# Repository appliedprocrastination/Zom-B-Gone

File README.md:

# Zom-B-Gone

Code for a very basic DIY Wake-up Light. 

This code uses an Arduino Nano (Uno would also work)
It assumes that an Adafruit DS3231 RTC module is connected to the following pins:
 * SDA = A4
 * SCL = A5
 * SQW = D3

The code further assumes a rotary encoder connected to the following pins:
 * CLK = A0
 * DT = A1
 * SW = A2

It is finally assumed that an ULN2803N is connected to pin D6, and that there is a button connected to pin D2.
The button used in the original code includes an LED that is connected to pin D6,
and connecting an LED to this pin will indicate whenever the WakeUpLight is in manual override mode.

To change the alarm settings, modify the `AlarmSettings` struct with your preffered values. Current behavior of the wake-up light is to dim up for 30 minutes towards the START alarm and then down for 30 minutes towards the END alarm. This is inteded to be synced with an external alarm clock (eg. cell phone alarm).

Before first use: set the correct time on the RTC module and load it with a coin cell battery to retain this value through power cycles.

by:
[Applied Procrastination](https://www.youtube.com/AppliedProcrastination)

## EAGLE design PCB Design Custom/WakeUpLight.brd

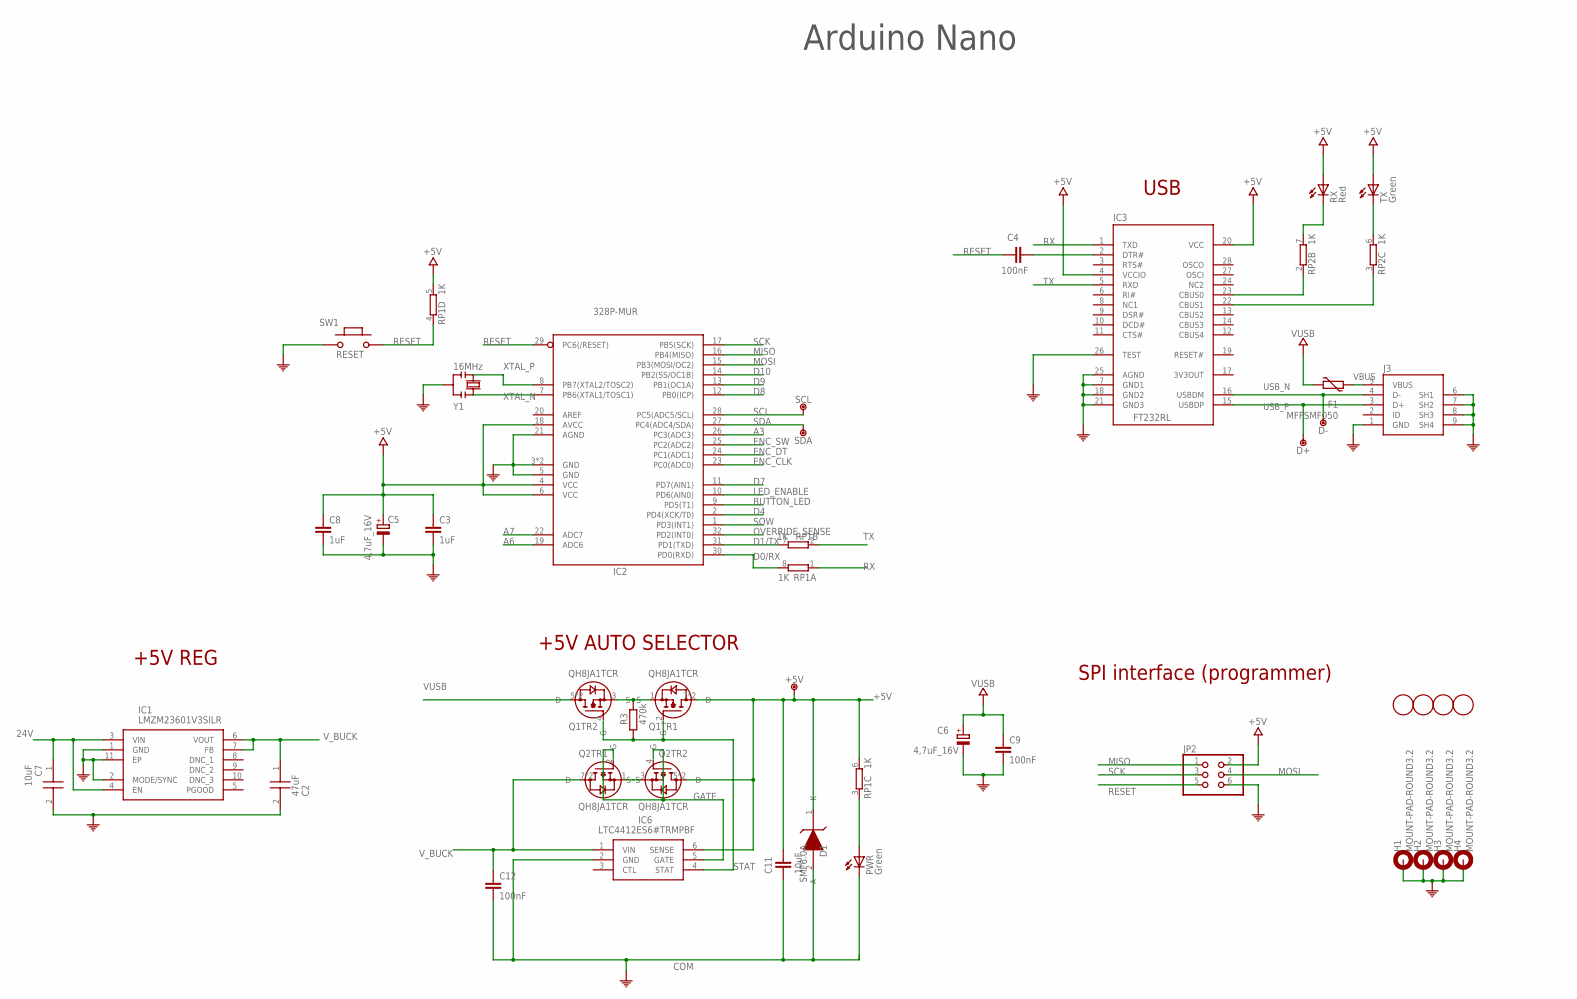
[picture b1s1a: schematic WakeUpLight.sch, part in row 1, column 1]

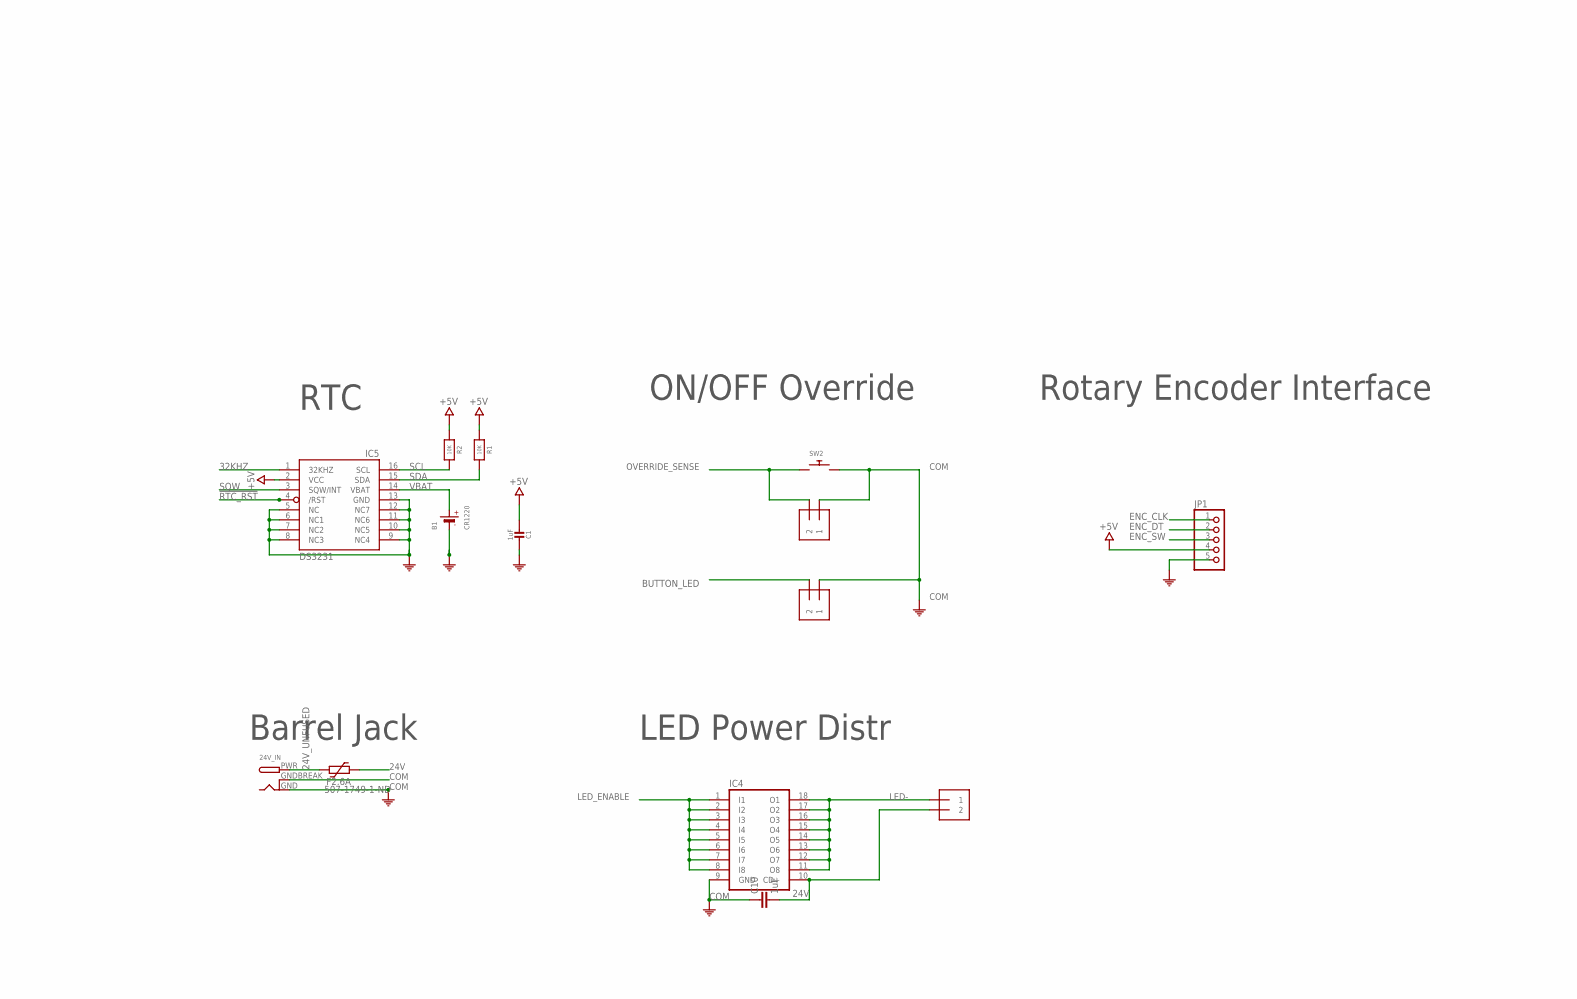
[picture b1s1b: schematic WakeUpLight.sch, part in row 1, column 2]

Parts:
24V_IN: DCBARRELPTH; DCJACK_2MM_PTH
+5V: DNP; TP-1.00MM
B1: CR1220
BUTTON_LED: 1X2-3.5MM
C1: 1uF; 0805-NO
C2: 47uF; CAPC3216X180N
C3, C8, C10: 1uF; C0603-ROUND
C4, C9, C12: 100nF; C0603-ROUND
C5, C6: 4,7uF_16V; TAN-A
C7: 10uF; CAPC2012X100N
C11: 10uF; C0603; MPN GRM188R61E106MA73D
D1: SMF6.0A; SODFL3618X108N
D+: DNP; TP-1.00MM
D-: DNP; TP-1.00MM
F1: MFFSMF050; 0603-1608X90N
F2.6A: 507-1749-1-ND; 2016L; MPN 0ZCF0200AF2C
H1, H2, H3, H4: MOUNT-PAD-ROUND3.2; 3,2-PAD
IC1: LMZM23601V3SILR; LMZM23600SILT
IC2: 328P-MUR; VQFN32
IC3: FT232RL; SSOP28
IC4: ULN2803ASMT; SO18W
IC5: DS3231/SO; SO16W
IC6: LTC4412ES6#TRMPBF; SOT95P280X100-6N
J3: 0219_14850; USB-MINI-B_2
JP1: PINHD-1X5; 1X05
JP2: 0114_PH254-203DF118A00V; 2X03
LED: 1X2-3.5MM
OVERRIDE: 1X2-3.5MM
PWR: Green; CHIPLED_0805
Q1, Q2: QH8JA1TCR; SOTFL65P280X85-8N
R1, R2: 10K; 0805-NO
R3: 470k; R0603
RP1, RP2: 1K; CAY16
RX: Red; CHIPLED_0805
SCL: DNP; TP-1.00MM
SDA: DNP; TP-1.00MM
SW1: RESET; SMD_157SW
SW2: SWITCH_PUSHBUTTONSOFTTOUCHSMD_SJ; PUSHBUTTON_SMD_SJ
TX: Green; CHIPLED_0805
U$36, U$39, U$53, U$54: DNP; FD-1-1.5
Y1: 16MHz; RESONATOR

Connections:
3V3OUT: IC3.17 (3V3OUT)
24V: C7.1, C10.2, F2.6A.2, IC1.3 (VIN), IC1.4 (EN), IC4.10 (CD+), LED.2
24V_UNFUSED: 24V_IN.PWR, F2.6A.1
32KHZ: IC5.1 (32KHZ)
!RTC_RST: IC5.4 (/RST)
+5V: +5V.X, C1.2, C3.1, C5.1 (+), C8.1, C11.1, D1.1 (K), IC2.4 (VCC), IC2.6 (VCC), IC2.18 (AVCC), IC3.4 (VCCIO), IC3.20 (VCC), IC5.2 (VCC), IC6.6 (SENSE), JP1.4, JP2.2, Q1.7 (D), Q1.8 (D), Q2.5 (D), Q2.6 (D), R1.1, R2.1, RP1.5 (2), RP1.6 (2), RX.A, TX.A
A3: IC2.26 (PC3(ADC3))
A6: IC2.19 (ADC6)
A7: IC2.22 (ADC7)
BUTTON_LED: BUTTON_LED.2, IC2.9 (PD5(T1))
COM: 24V_IN.GND, 24V_IN.GNDBREAK, B1.-, BUTTON_LED.1, C1.1, C2.2, C3.2, C5.2 (-), C6.2 (-), C7.2, C8.2, C9.2, C10.1, C11.2, C12.2, D1.2 (A), H1.B3,2, H2.B3,2, H3.B3,2, H4.B3,2, IC1.1 (GND), IC1.2 (MODE/SYNC), IC1.11 (EP), IC2.3 (GND), IC2.5 (GND), IC2.21 (AGND), IC2.33 (GND), IC3.7 (GND1), IC3.18 (GND2), IC3.21 (GND3), IC3.25 (AGND), IC3.26 (TEST), IC4.9 (GND), IC5.5 (NC), IC5.6 (NC1), IC5.7 (NC2), IC5.8 (NC3), IC5.9 (NC4), IC5.10 (NC5), IC5.11 (NC6), IC5.12 (NC7), IC5.13 (GND), IC6.2 (GND), J3.1 (GND), J3.6 (SH1), J3.7 (SH2), J3.8 (SH3), J3.9 (SH4), JP1.5, JP2.6, OVERRIDE.1, PWR.C, SW1.1, SW2.P$2, Y1.2
D0/RX: IC2.30 (PD0(RXD)), RP1.8 (2)
D1/TX: IC2.31 (PD1(TXD)), RP1.7 (2)
D4: IC2.2 (PD4(XCK/T0))
D7: IC2.11 (PD7(AIN1))
D8: IC2.12 (PB0(ICP))
D9: IC2.13 (PB1(OC1A))
D10: IC2.14 (PB2(SS/OC1B))
ENC_CLK: IC2.23 (PC0(ADC0)), JP1.1
ENC_DT: IC2.24 (PC1(ADC1)), JP1.2
ENC_SW: IC2.25 (PC2(ADC2)), JP1.3
GATE: IC6.5 (GATE), Q2.2 (G), Q2.4 (G)
LED-: IC4.11 (O8), IC4.12 (O7), IC4.13 (O6), IC4.14 (O5), IC4.15 (O4), IC4.16 (O3), IC4.17 (O2), IC4.18 (O1), LED.1
LED_ENABLE: IC2.10 (PD6(AIN0)), IC4.1 (I1), IC4.2 (I2), IC4.3 (I3), IC4.4 (I4), IC4.5 (I5), IC4.6 (I6), IC4.7 (I7), IC4.8 (I8)
MISO: IC2.16 (PB4(MISO)), JP2.1
MOSI: IC2.15 (PB3(MOSI/OC2)), JP2.4
unnamed: Q1.1 (S), Q1.3 (S), R3.2
unnamed: PWR.A, RP1.3 (1)
unnamed: C4.2, IC3.2 (DTR#)
unnamed: IC3.23 (CBUS0), RP2.2 (1)
unnamed: IC3.22 (CBUS1), RP2.3 (1)
unnamed: RP2.6 (2), TX.C
unnamed: Q2.1 (S), Q2.3 (S)
unnamed: RP2.7 (2), RX.C
OVERRIDE_SENSE: IC2.32 (PD2(INT0)), OVERRIDE.2, SW2.P$1
RESET: C4.1, IC2.29 (PC6(/RESET)), JP2.5, RP1.4 (1), SW1.2
RX: IC3.1 (TXD), RP1.1
SCK: IC2.17 (PB5(SCK)), JP2.3
SCL: IC2.28 (PC5(ADC5/SCL)), IC5.16 (SCL), R2.2, SCL.X
SDA: IC2.27 (PC4(ADC4/SDA)), IC5.15 (SDA), R1.2, SDA.X
SQW: IC2.1 (PD3(INT1)), IC5.3 (SQW/INT)
STAT: IC6.4 (STAT), Q1.2 (G), Q1.4 (G), R3.1
TX: IC3.5 (RXD), RP1.2 (1)
USB_N: D-.X, IC3.16 (USBDM), J3.4 (D-)
USB_P: D+.X, IC3.15 (USBDP), J3.3 (D+)
VBAT: B1.+$1 (+), IC5.14 (VBAT)
VBUS: F1.2, J3.5 (VBUS)
VUSB: C6.1 (+), C9.1, F1.1, Q1.5 (D), Q1.6 (D)
V_BUCK: C2.1, C12.1, IC1.6 (VOUT), IC1.7 (FB), IC6.1 (VIN), Q2.7 (D), Q2.8 (D)
XTAL_N: IC2.7 (PB6(XTAL1/TOSC1)), Y1.1
XTAL_P: IC2.8 (PB7(XTAL2/TOSC2)), Y1.3

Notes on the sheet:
RTC
+5V REG
USB
Barrel Jack
LED Power Distr
ON/OFF Override
Arduino Nano
SPI interface (programmer)
+5V AUTO SELECTOR
Rotary Encoder Interface

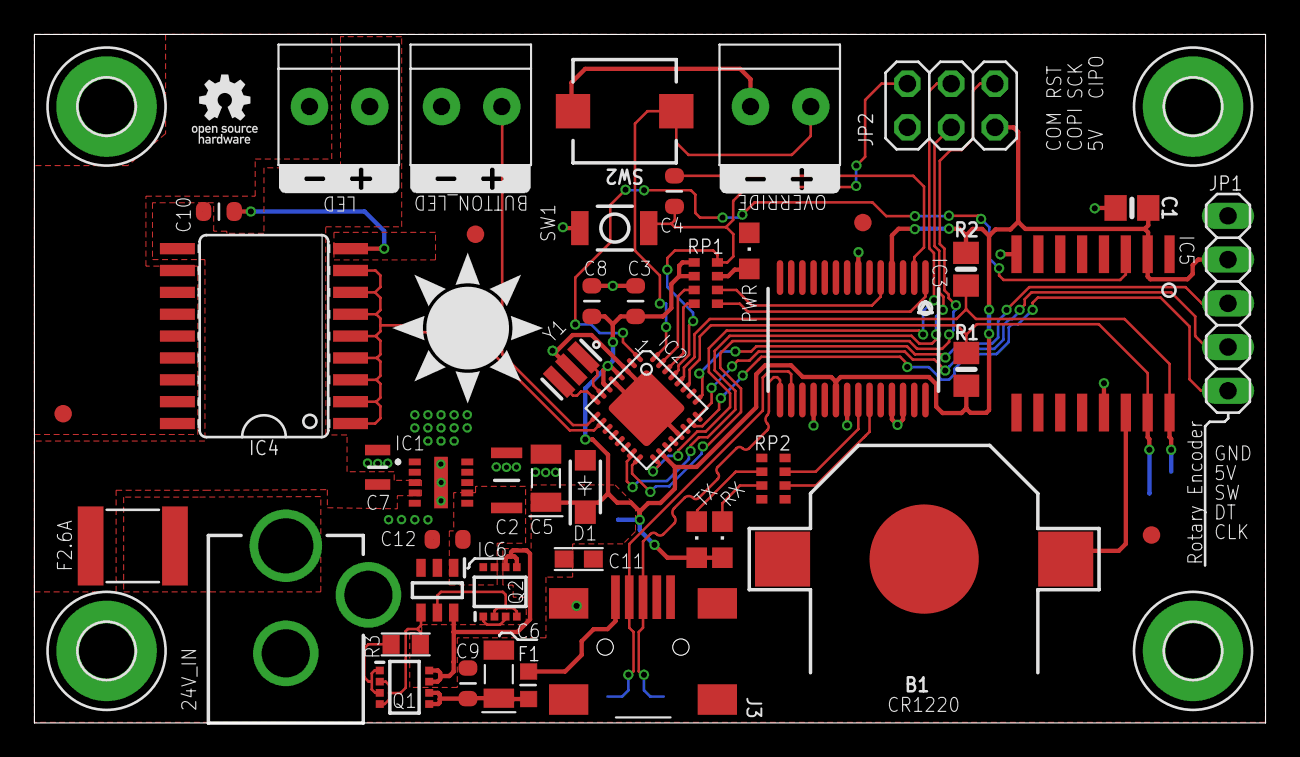
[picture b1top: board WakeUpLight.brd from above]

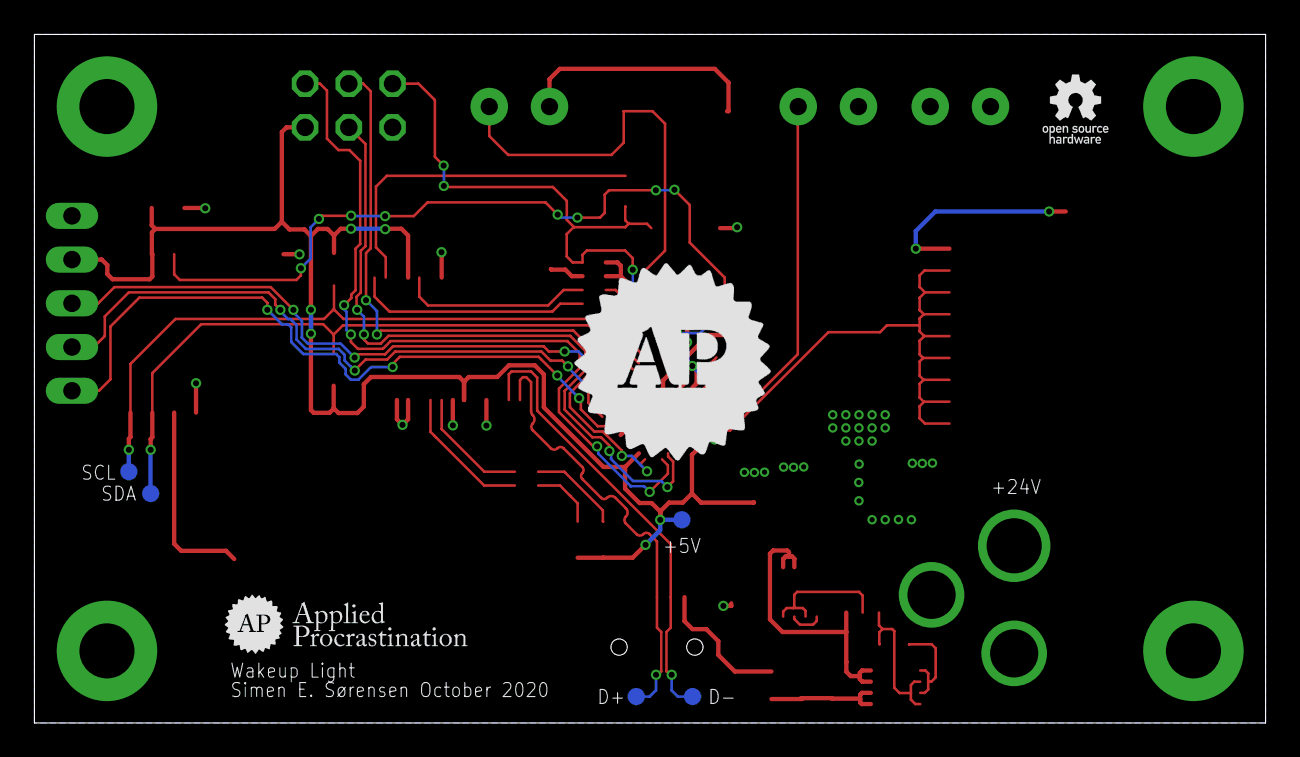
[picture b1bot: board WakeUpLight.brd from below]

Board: 2 copper layers, 71.5 x 40.0 mm, 63 parts (3 on the bottom side), 40 nets.

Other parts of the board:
U$15: APPLIED-PROC
U$19: APPLIED-PROCRASTINATION-FULL-SMALL
U$33: WAKEUP-LIGHT-LOGO2
U$34, U$38, U$41: TB-PLUSMINUS-FLIP
U$37, U$42: OSHW-LOGO

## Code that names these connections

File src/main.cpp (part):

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 * It assumes that an Adafruit DS3231 RTC module is connected to the following pins:
 * SDA = A4
 * SCL = A5
 * SQW = D3
 * The code further assumes a rotary encoder connected to the following pins:
 * CLK = A0
 * DT = A1
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
volatile boolean MANUAL_OVERRIDE, OVERRIDE_SENSE_FLAG;

static const uint8_t ENC_CLK_PIN = A0;
static const uint8_t ENC_DT_PIN = A1;
static const uint8_t ENC_SW_PIN = A2;

static const uint8_t OVERRIDE_SENSE_PIN = 2;
static const uint8_t CLOCK_INTERRUPT_PIN = 3;
static const uint8_t BUTTON_LED_PIN = 5;
static const uint8_t LED_ENABLE_PIN = 6;

static const int BUTTON_LED_PWM_VALUE = 255; //TODO: Set this value lower if the button is too bright.
static const int MAX_ENCODER_VALUE = 50;   //This value is mapped down to 255 before being used. TODO: Tune this value in case the encoder feels too slow.
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  rtc.clearAlarm(1);
  rtc.clearAlarm(2);

  // stop oscillating signals at SQW Pin
  // otherwise setAlarm1 will fail
  rtc.writeSqwPinMode(DS3231_OFF);
  char buf1[] = "RTC Time: DD MM YYYY-hh:mm:ss";
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{
  Serial.begin(9600);
  // Set up encoder
  encoder = new ClickEncoder(ENC_DT_PIN, ENC_CLK_PIN, ENC_SW_PIN, 2);
  initRotaryEncoder();
  Timer1.stop(); //Stop the rotary encoder readings until the manual override mode is activated in order to save power
  // Set up RTC
  initRTC();
  // Set up inputs
  pinMode(OVERRIDE_SENSE_PIN, INPUT_PULLUP);
  // Set up interrupt on input
  attachInterrupt(digitalPinToInterrupt(OVERRIDE_SENSE_PIN), overrideSenseIsr, FALLING);
  interrupts();
  // Set up outputs
  pinMode(BUTTON_LED_PIN, OUTPUT);
  pinMode(LED_ENABLE_PIN, OUTPUT);
  analogWrite(BUTTON_LED_PIN, 0);
  analogWrite(LED_ENABLE_PIN, 0);
  //Init variables
  MANUAL_OVERRIDE = false;
  OVERRIDE_SENSE_FLAG = false;
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      Serial.println("Override button released, light OFF! (Alarms are active)");
      Timer1.stop(); //Stop the rotary encoder readings to save power
      OVERRIDE_SENSE_FLAG = false;
      analogWrite(BUTTON_LED_PIN, 0);
      Serial.print("Writing PWM ");
      Serial.print(0);
      Serial.println(" to LED driver.");
      analogWrite(LED_ENABLE_PIN, 0);


    }
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            dimming_up = false;
            Serial.println("Done dimming up.");
          }
          analogWrite(LED_ENABLE_PIN,auto_pwm_value);
        }
        else if (dimming_down){
          auto_pwm_value = constrain(auto_pwm_value - pwm_dimming_delta, ALARM_SETTINGS.MIN_PWM, ALARM_SETTINGS.MAX_PWM);
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            Serial.println("Done dimming down.");
            dimming_down = false;
          }
          analogWrite(LED_ENABLE_PIN, auto_pwm_value);
        }
        timestamp_prev_pwm_change = timenow;
      }
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      
      Serial.println("Overriding alarms, light ON!");
      Timer1.start();
      analogWrite(BUTTON_LED_PIN,BUTTON_LED_PWM_VALUE);
      OVERRIDE_SENSE_FLAG = false;
    }
    acquireRotaryEncoderPos();
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      Serial.print("Writing PWM ");
      Serial.print(manual_pwm_value);
      Serial.println(" to LED driver.");
      analogWrite(LED_ENABLE_PIN,manual_pwm_value);
      last_manual_pwm_value = manual_pwm_value;
    }
  }
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
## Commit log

2020-10-06 Initial Commit
    All code is completely untested as the hardware has not arrived yet.
2021-05-27 Initial testing with real hardware
    Fixing some bugs that showed up during real-life testing. Tweaked some values and renamed some variables to clean up code.
2021-09-01 Update main.cpp
    Exclude saturday and sunday from alarm list, and fix bug that caused this to fail previously.
2021-09-13 Create License
2021-09-13 Added PCB Design files
2021-09-13 Add 3D Printed Parts
    Step model

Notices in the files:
parts and their libraries:
microbuilder: This work is placed in the public domain, and may be freely used for commercial and non-commercial work with the following conditions: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
Arduino-utility: Copyright (c) 2016-2017 Arduino LLC.  All right reserved.
